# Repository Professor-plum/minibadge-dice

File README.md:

# minibadge-dice
SaintCon D6 roller minibadge

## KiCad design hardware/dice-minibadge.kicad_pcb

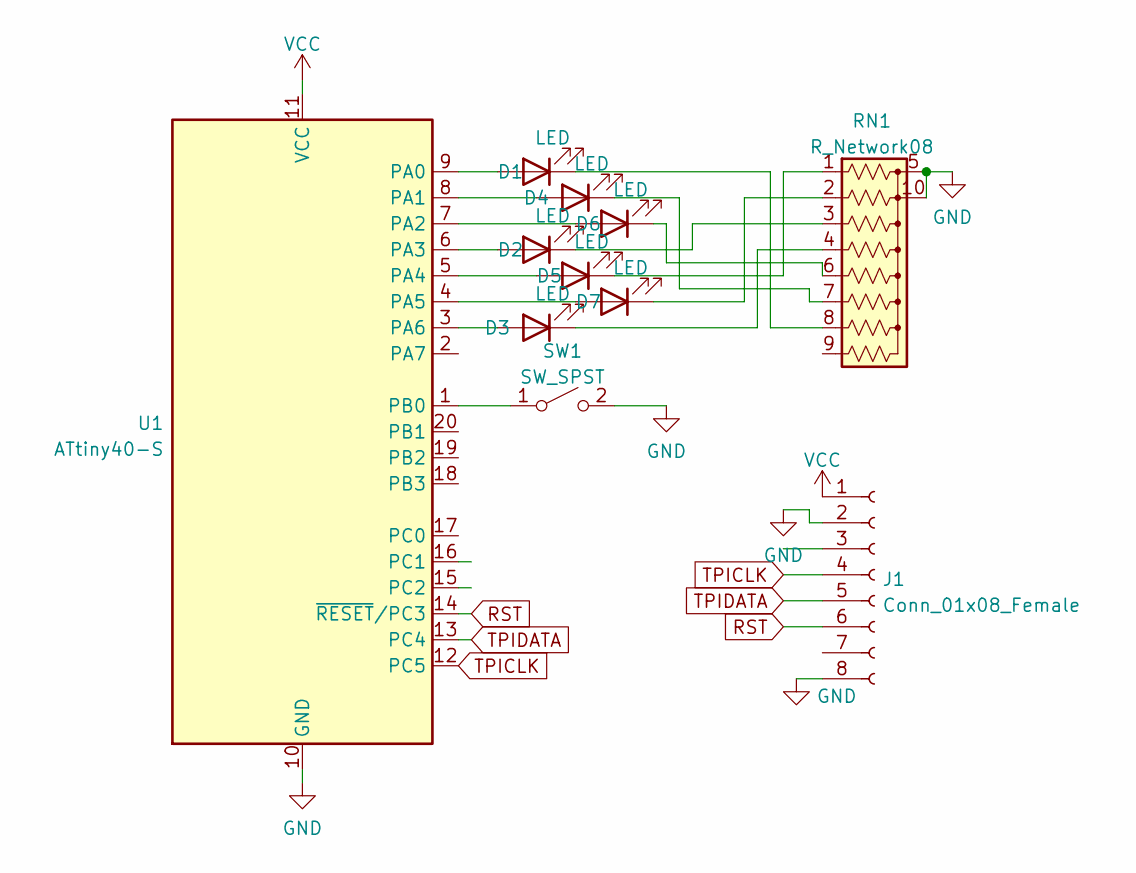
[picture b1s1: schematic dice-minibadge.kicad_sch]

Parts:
D1, D2, D3, D4, D5, D6, D7: LED; LED_0805_2012Metric_Pad1.15x1.40mm_HandSolder
J1: Conn_01x08_Female; PinHeader_1x08_P2.54mm_Vertical
RN1: R_Network08; R_Array_Convex_5x1206
SW1: SW_SPST; SW_SPST_EVQP7A
U1: ATtiny40-S; SOIC-20W_7.5x12.8mm_P1.27mm

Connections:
GND: J1.2, J1.8, RN1.5 (common), RN1.10 (common), SW1.2 (B), U1.10 (GND)
unnamed: D1.1 (K), RN1.8 (R7)
unnamed: D1.2 (A), U1.9 (PA0)
unnamed: D2.1 (K), RN1.3 (R3)
unnamed: D2.2 (A), U1.6 (PA3)
unnamed: D3.1 (K), RN1.4 (R4)
unnamed: D3.2 (A), U1.3 (PA6)
unnamed: D4.1 (K), RN1.7 (R6)
unnamed: D4.2 (A), U1.8 (PA1)
unnamed: D5.1 (K), RN1.1 (R1)
unnamed: D5.2 (A), U1.5 (PA4)
unnamed: D6.1 (K), RN1.6 (R5)
unnamed: D6.2 (A), U1.7 (PA2)
unnamed: D7.1 (K), RN1.2 (R2)
unnamed: D7.2 (A), U1.4 (PA5)
unnamed: SW1.1 (A), U1.1 (PB0)
RST: J1.6, U1.14 (~RESET/PC3)
TPICLK: J1.4, U1.12 (PC5)
TPIDATA: J1.5, U1.13 (PC4)
VCC: J1.1, U1.11 (VCC)

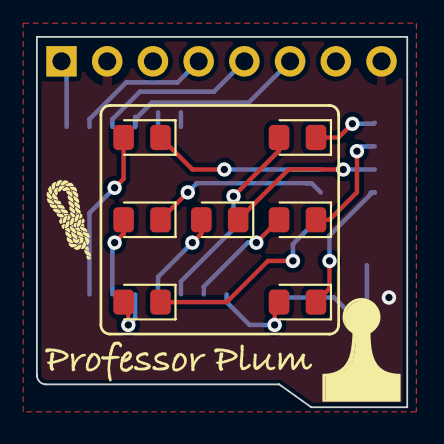
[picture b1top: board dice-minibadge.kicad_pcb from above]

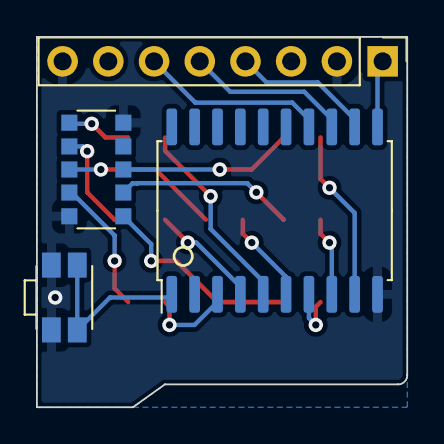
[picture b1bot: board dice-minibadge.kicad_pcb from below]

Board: 2 copper layers, 20.6 x 20.6 mm, 11 parts (4 on the bottom side), 20 nets.

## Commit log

2022-11-14 Adding firmare, hardware, and image content
